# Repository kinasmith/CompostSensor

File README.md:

# Compost Sensor

> Compost Sensor is an open source sensor system for monitoring and recording the temperature and moisture of active compost. It is for small scale commercial composting operations to help with quality control and the certification processes.

This is a currently work in progress. Blog updates can be found [here](http://www.kinasmith.com/itp/spring2015/thesis/).

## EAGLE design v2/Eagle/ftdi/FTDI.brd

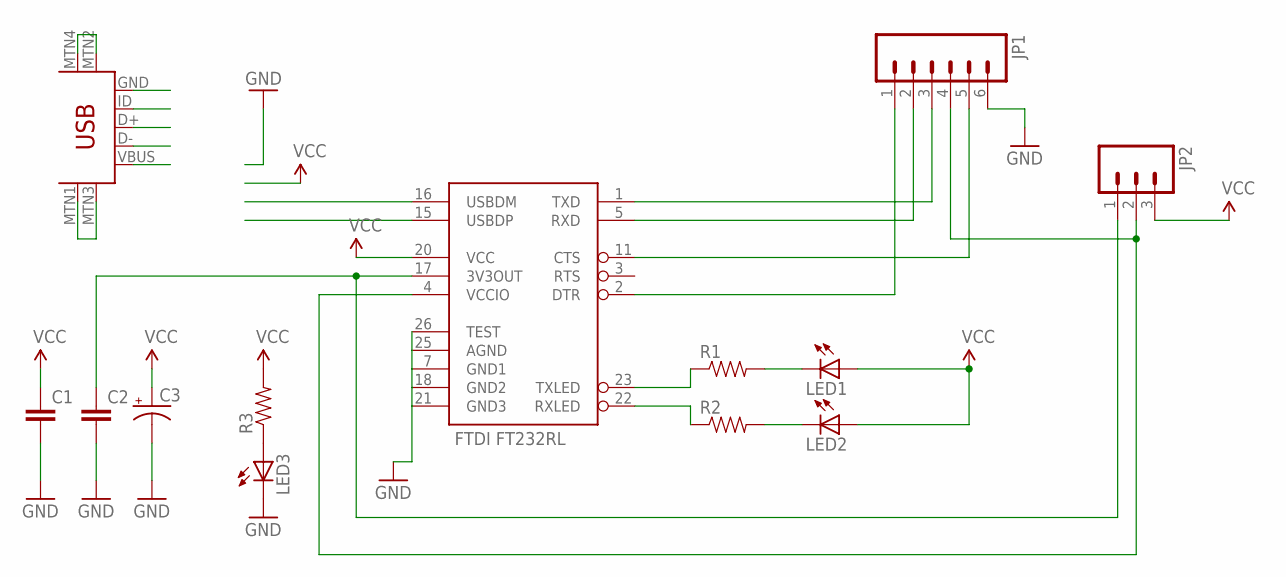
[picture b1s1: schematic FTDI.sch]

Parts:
C1, C2: CAP0603-CAP; 0603-CAP
C3: CAP_POL1206; EIA3216
JP1: M06SIP; 1X06
JP2: M03PTH; 1X03
LED1, LED2, LED3: LED0603; LED-0603
R1, R2, R3: RESISTOR0603-RES; 0603-RES
U1: FT232RL-BASICSSOP; SSOP28DB
U$3: USB-MINIB-5PIN; USB-MINIB

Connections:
D+: U1.15 (USBDP), U$3.D+
D-: U1.16 (USBDM), U$3.D-
GND: C1.2, C2.2, C3.C (-), JP1.6, LED3.C, U1.7 (GND1), U1.18 (GND2), U1.21 (GND3), U1.25 (AGND), U1.26 (TEST), U$3.GND, U$3.MTN1 (MTN2), U$3.MTN2 (MTN3), U$3.MTN3 (MTN1), U$3.MTN4
unnamed: R1.1, U1.23 (TXLED)
unnamed: LED1.C, R1.2
unnamed: LED2.C, R2.2
unnamed: R2.1, U1.22 (RXLED)
unnamed: JP1.1, U1.2 (DTR)
unnamed: JP1.2, U1.5 (RXD)
unnamed: JP1.3, U1.1 (TXD)
unnamed: JP1.5, U1.11 (CTS)
unnamed: JP1.4, JP2.2, U1.4 (VCCIO)
unnamed: C2.1, JP2.1, U1.17 (3V3OUT)
unnamed: LED3.A, R3.1
VCC: C1.1, C3.A (+), JP2.3, LED1.A, LED2.A, R3.2, U1.20 (VCC), U$3.VBUS

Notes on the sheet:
FTDI FT232RL

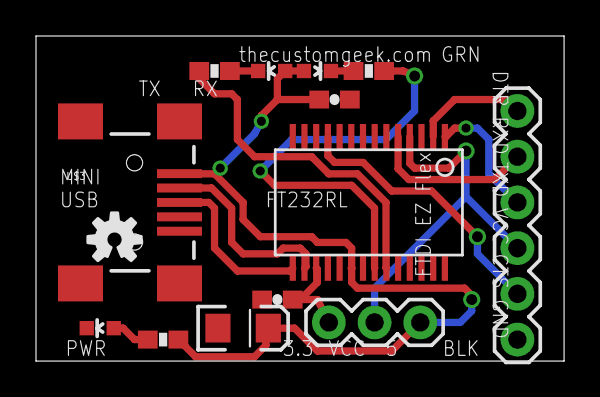
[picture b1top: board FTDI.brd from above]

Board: 2 copper layers, 29.3 x 18.1 mm, 15 parts (1 on the bottom side), 15 nets.

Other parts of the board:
U$1, U$2: OSHW-LOGO-S

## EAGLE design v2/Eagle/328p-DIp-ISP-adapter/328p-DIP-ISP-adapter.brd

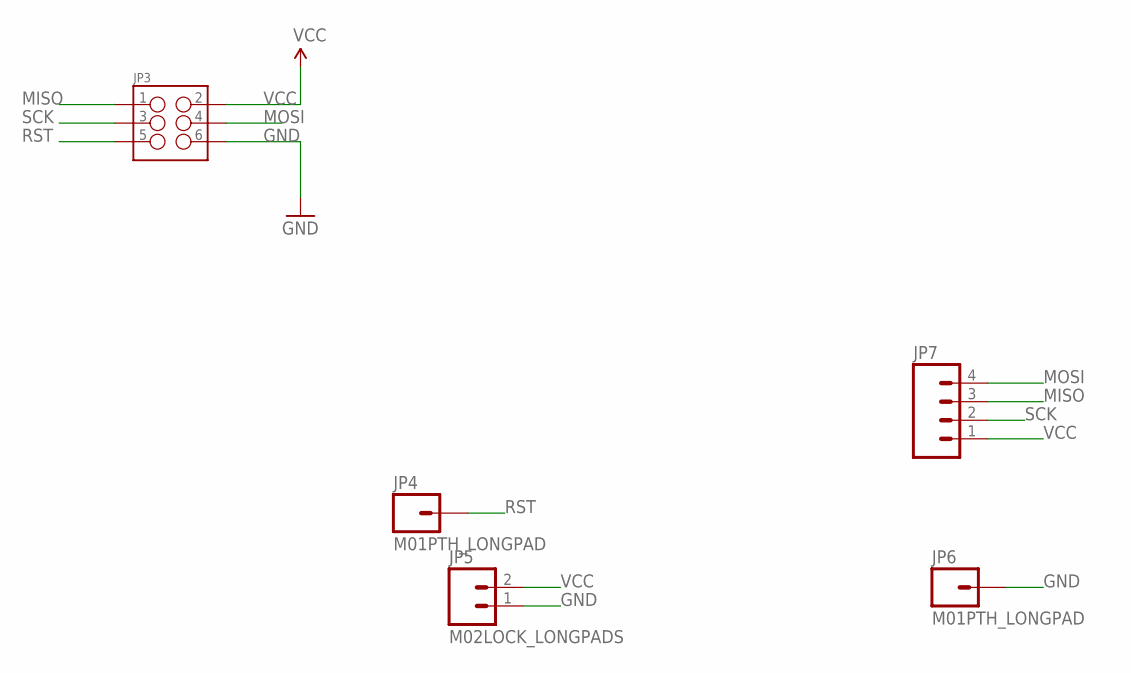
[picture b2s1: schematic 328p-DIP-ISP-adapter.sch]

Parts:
JP3: M03X2SMT; 2X3_SMT_POSTS
JP4, JP6: M01PTH_LONGPAD; 1X01_LONGPAD
JP5: M02LOCK_LONGPADS; 1X02_LOCK_LONGPADS
JP7: M04LOCK_LONGPADS; 1X04_LOCK_LONGPADS

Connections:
GND: JP3.6, JP5.1, JP6.1
MISO: JP3.1, JP7.3
MOSI: JP3.4, JP7.4
RST: JP3.5, JP4.1
SCK: JP3.3, JP7.2
VCC: JP3.2, JP5.2, JP7.1

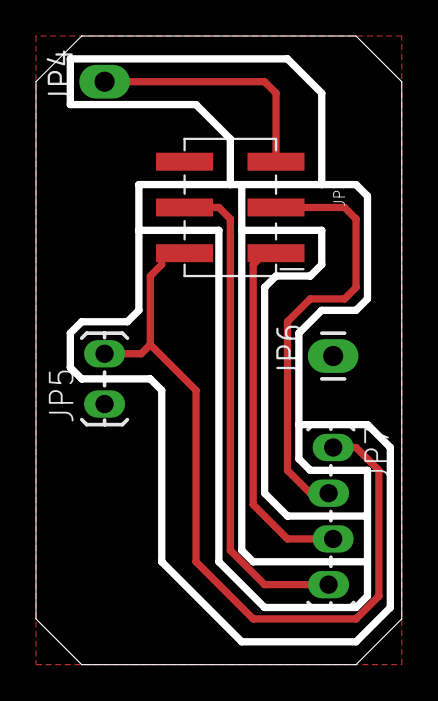
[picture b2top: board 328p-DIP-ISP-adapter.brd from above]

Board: 2 copper layers, 19.9 x 34.5 mm, 5 parts (0 on the bottom side), 6 nets.

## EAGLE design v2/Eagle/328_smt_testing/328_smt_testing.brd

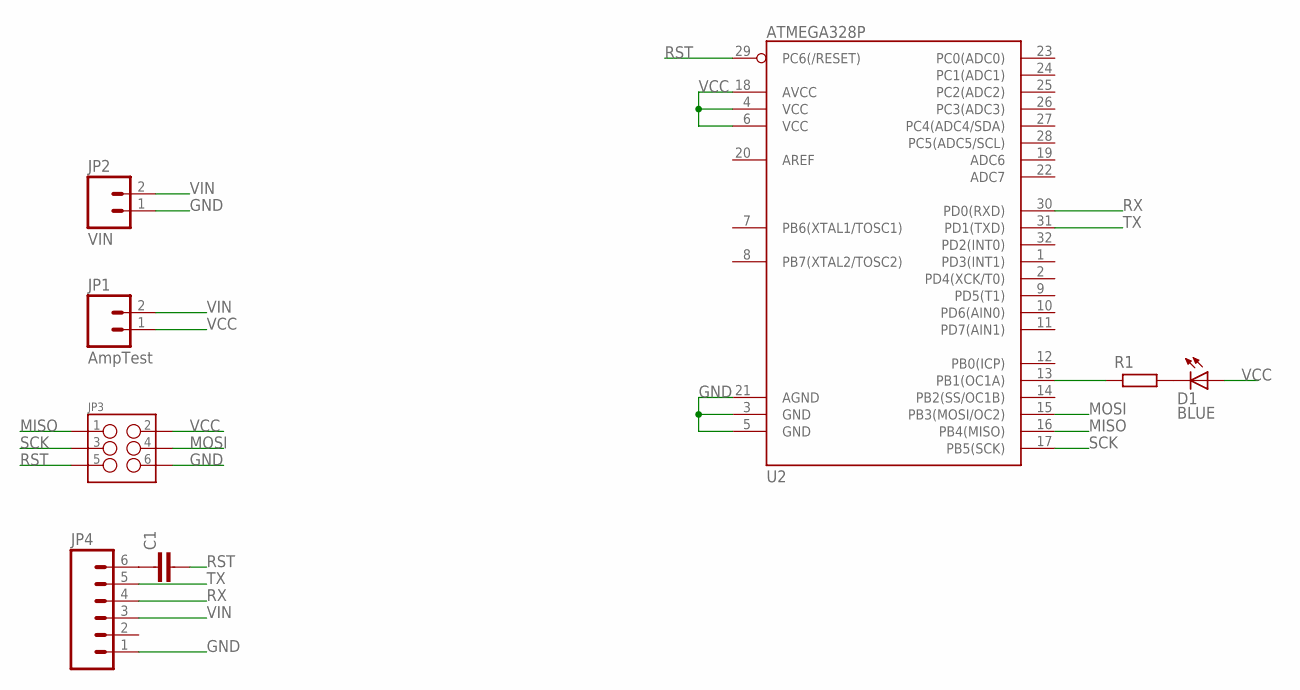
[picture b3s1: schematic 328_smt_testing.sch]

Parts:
C1: CAPACITOR0603-N; C0603-N
D1: BLUE; LED-0603
JP1: AmpTest; 1X02_LOCK_LONGPADS
JP2: VIN; 1X02_LOCK_LONGPADS
JP3: M03X2FEMALE_SMD; 2X3_SMD
JP4: M06LOCK_LONGPADS; 1X06_LOCK_LONGPADS
R1: RESISTOR0603-L; R0603-L
U2: ATMEGA328P; TQFP32-08

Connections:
GND: JP2.1, JP3.6, JP4.1, U2.3 (GND), U2.5 (GND), U2.21 (AGND)
MISO: JP3.1, U2.16 (PB4(MISO))
MOSI: JP3.4, U2.15 (PB3(MOSI/OC2))
unnamed: D1.C, R1.2
unnamed: C1.1, JP4.6
unnamed: R1.1, U2.13 (PB1(OC1A))
RST: C1.2, JP3.5, U2.29 (PC6(/RESET))
RX: JP4.4, U2.30 (PD0(RXD))
SCK: JP3.3, U2.17 (PB5(SCK))
TX: JP4.5, U2.31 (PD1(TXD))
VCC: D1.A, JP1.1, JP3.2, U2.4 (VCC), U2.6 (VCC), U2.18 (AVCC)
VIN: JP1.2, JP2.2, JP4.3

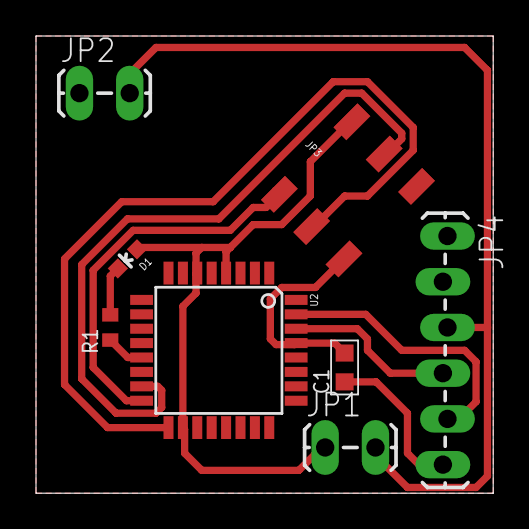
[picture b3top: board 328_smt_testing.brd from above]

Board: 2 copper layers, 25.4 x 25.4 mm, 8 parts (0 on the bottom side), 12 nets.

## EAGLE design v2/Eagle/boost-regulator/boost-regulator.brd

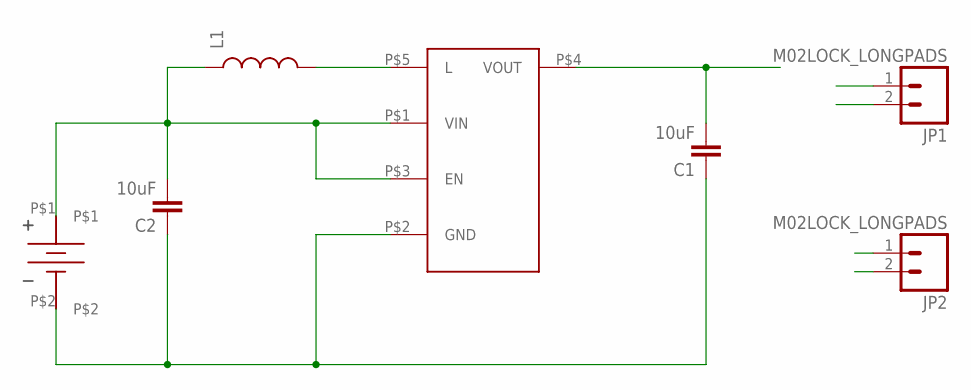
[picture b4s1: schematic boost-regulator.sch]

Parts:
C1, C2: 10uF; 0603-CAP
JP1, JP2: M02LOCK_LONGPADS; 1X02_LOCK_LONGPADS
L1: INDUCTOR0603; 0603
U$1: KEYSTONEAAHOLDER_2CELL
U$2: TPS61097-33; SOT23-5

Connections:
GND: C1.1, C2.1, JP1.2, JP2.2, U$1.P$2, U$2.P$2 (GND)
unnamed: L1.2, U$2.P$5 (L)
VCC: C1.2, JP1.1, JP2.1, U$2.P$4 (VOUT)
VIN: C2.2, L1.1, U$1.P$1, U$2.P$1 (VIN), U$2.P$3 (EN)

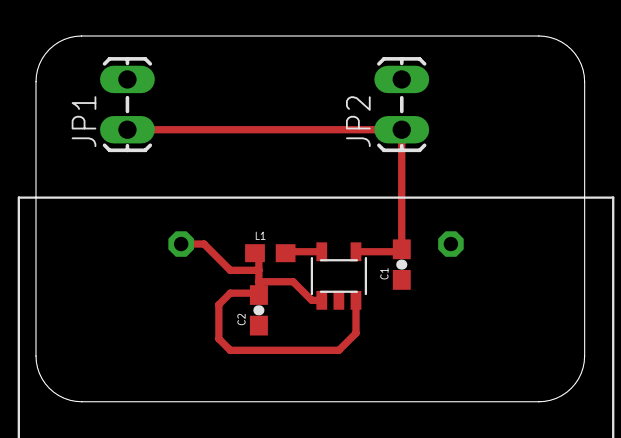
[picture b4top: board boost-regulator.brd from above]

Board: 2 copper layers, 30.5 x 20.3 mm, 7 parts (0 on the bottom side), 4 nets.

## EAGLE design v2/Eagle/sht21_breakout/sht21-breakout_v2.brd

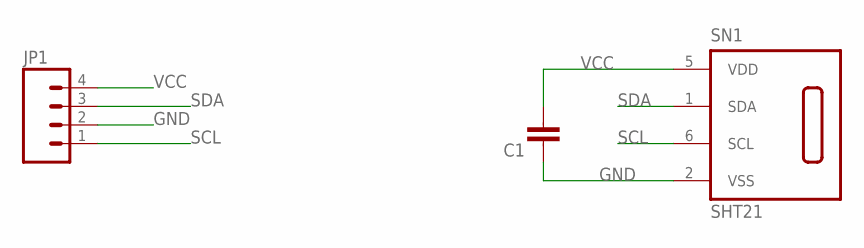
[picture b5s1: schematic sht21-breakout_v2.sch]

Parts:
C1: CAPACITOR0603-N; C0603-N
JP1: M04LONGPADS; 1X04_LONGPADS
SN1: SHT21; DFN6/SHT

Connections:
GND: C1.1, JP1.2, SN1.2 (VSS)
SCL: JP1.1, SN1.6 (SCL)
SDA: JP1.3, SN1.1 (SDA)
VCC: C1.2, JP1.4, SN1.5 (VDD)

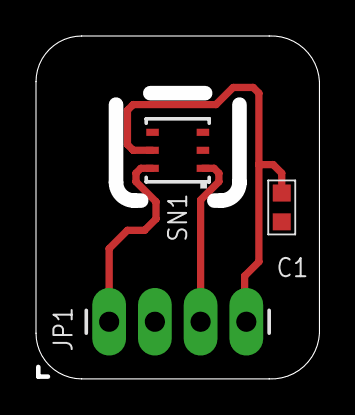
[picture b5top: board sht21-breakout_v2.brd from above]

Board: 2 copper layers, 14.9 x 18.2 mm, 3 parts (0 on the bottom side), 4 nets.

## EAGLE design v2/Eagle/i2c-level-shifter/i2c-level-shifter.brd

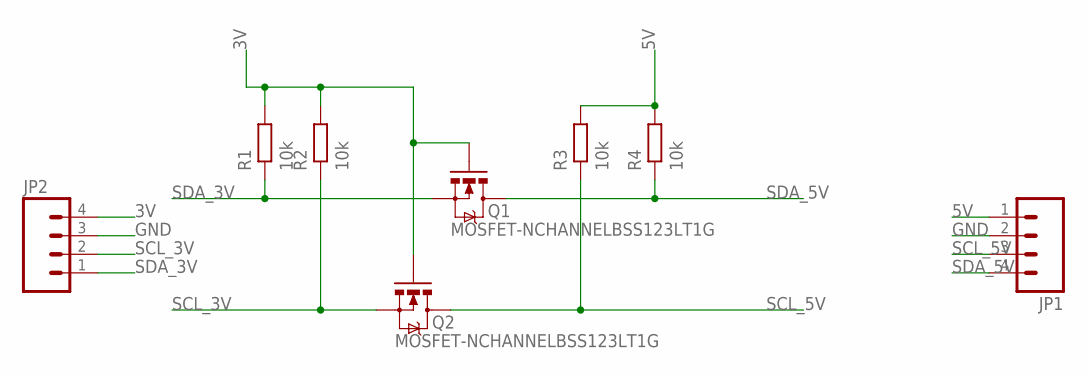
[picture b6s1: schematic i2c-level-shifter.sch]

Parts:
JP1, JP2: M04LOCK_LONGPADS; 1X04_LOCK_LONGPADS
Q1, Q2: MOSFET-NCHANNELBSS123LT1G; SOT23
R1, R2, R3, R4: 10k; R0603-N; MPN CRCW040210K0FKED

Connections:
3V: JP2.4, Q1.1 (G), Q2.1 (G), R1.2, R2.2
5V: JP1.1, R3.2, R4.2
GND: JP1.2, JP2.3
SCL_3V: JP2.2, Q2.2 (S), R2.1
SCL_5V: JP1.3, Q2.3 (D), R3.1
SDA_3V: JP2.1, Q1.2 (S), R1.1
SDA_5V: JP1.4, Q1.3 (D), R4.1

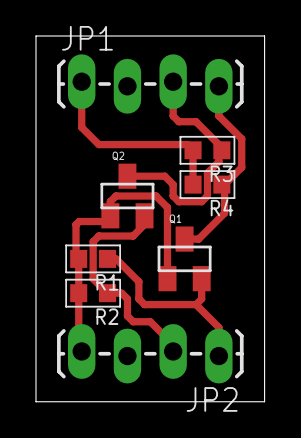
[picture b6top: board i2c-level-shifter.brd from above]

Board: 2 copper layers, 12.7 x 20.3 mm, 8 parts (0 on the bottom side), 7 nets.

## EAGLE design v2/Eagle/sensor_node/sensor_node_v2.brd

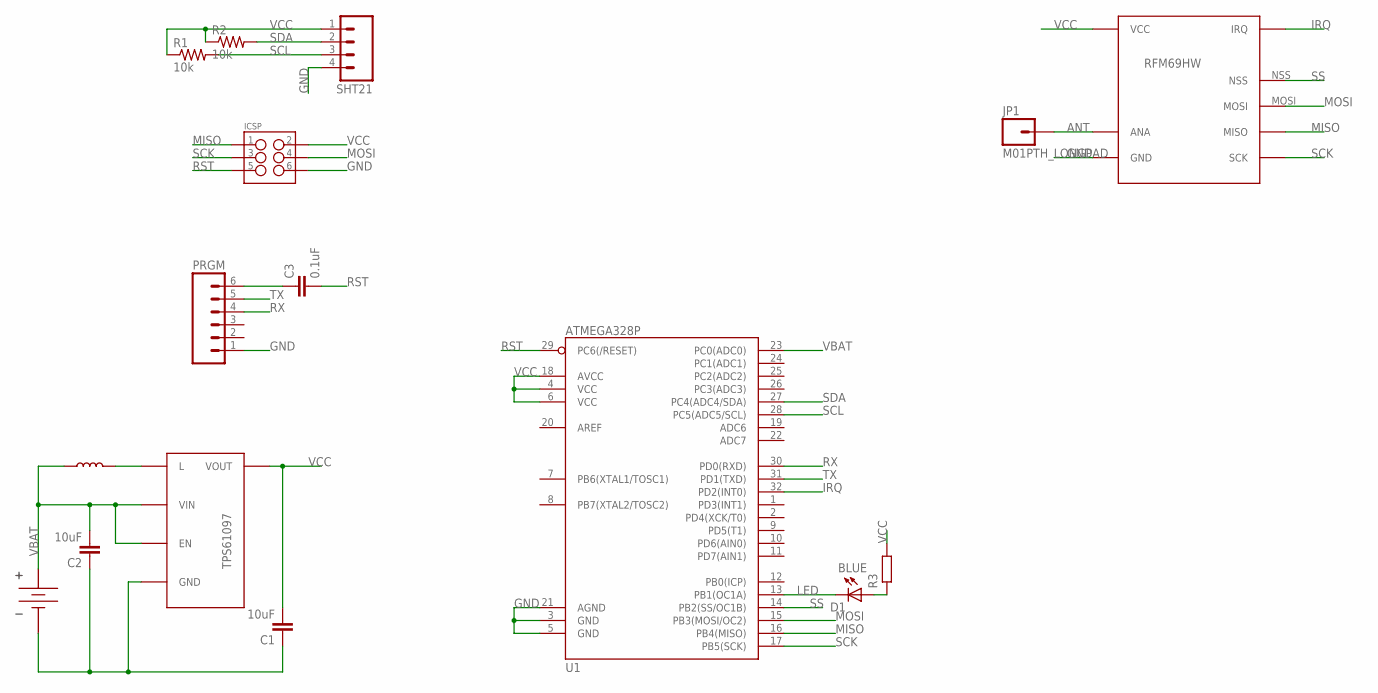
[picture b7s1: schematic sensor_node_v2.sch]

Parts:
C1, C2: 10uF; 0603-CAP
C3: 0.1uF; 0603-CAP
D1: BLUE; LED-0603
ICSP: M03X2FEMALE_SMD; 2X3_SMD
JP1: M01PTH_LONGPAD; 1X01_LONGPAD
PRGM: M06LOCK_LONGPADS; 1X06_LOCK_LONGPADS
R1, R2: 10k; 0603-RES
R3: RESISTOR0603-N; R0603-N
SHT21: M04LOCK_LONGPADS; 1X04_LOCK_LONGPADS
U1: ATMEGA328P; TQFP32-08
U$1: KEYSTONEAAHOLDER_2CELL
U$2: TPS61097-33; SOT23-5
U$3: COILCRAFT_DO3314
U$4: RFM69HW_MIN; RFM69

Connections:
ANT: JP1.1, U$4.ANA
GND: C1.1, C2.1, ICSP.6, PRGM.1, SHT21.4, U1.3 (GND), U1.5 (GND), U1.21 (AGND), U$1.P$2 (GND), U$2.P$2 (GND), U$4.GND
IRQ: U1.32 (PD2(INT0)), U$4.DIO0 (IRQ)
LED: D1.C, U1.13 (PB1(OC1A))
MISO: ICSP.1, U1.16 (PB4(MISO)), U$4.MISO
MOSI: ICSP.4, U1.15 (PB3(MOSI/OC2)), U$4.MOSI
unnamed: U$2.P$5 (L), U$3.P$1
unnamed: C3.1, PRGM.6
unnamed: D1.A, R3.1
RST: C3.2, ICSP.5, U1.29 (PC6(/RESET))
RX: PRGM.4, U1.30 (PD0(RXD))
SCK: ICSP.3, U1.17 (PB5(SCK)), U$4.SCK
SCL: R1.2, SHT21.3, U1.28 (PC5(ADC5/SCL))
SDA: R2.2, SHT21.2, U1.27 (PC4(ADC4/SDA))
SS: U1.14 (PB2(SS/OC1B)), U$4.NSS
TX: PRGM.5, U1.31 (PD1(TXD))
VBAT: C2.2, U1.23 (PC0(ADC0)), U$1.P$1 (VBAT), U$2.P$1 (VIN), U$2.P$3 (EN), U$3.P$2
VCC: C1.2, ICSP.2, R1.1, R2.1, R3.2, SHT21.1, U1.4 (VCC), U1.6 (VCC), U1.18 (AVCC), U$2.P$4 (VOUT), U$4.VCC

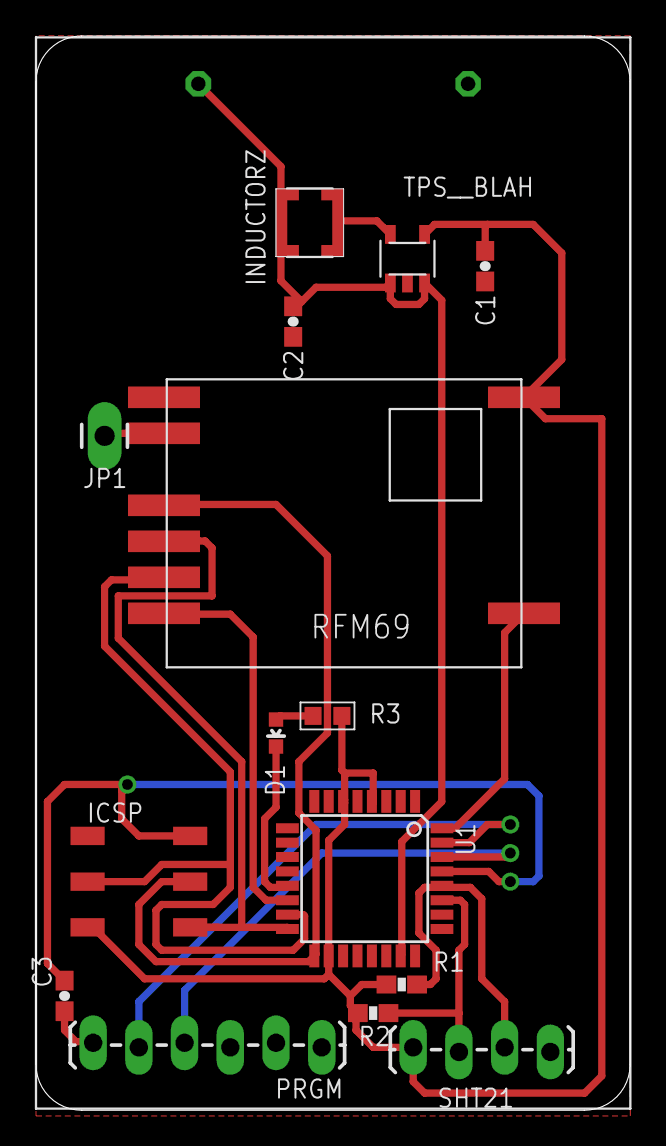
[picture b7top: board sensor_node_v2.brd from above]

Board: 2 copper layers, 33.0 x 59.7 mm, 16 parts (0 on the bottom side), 18 nets.

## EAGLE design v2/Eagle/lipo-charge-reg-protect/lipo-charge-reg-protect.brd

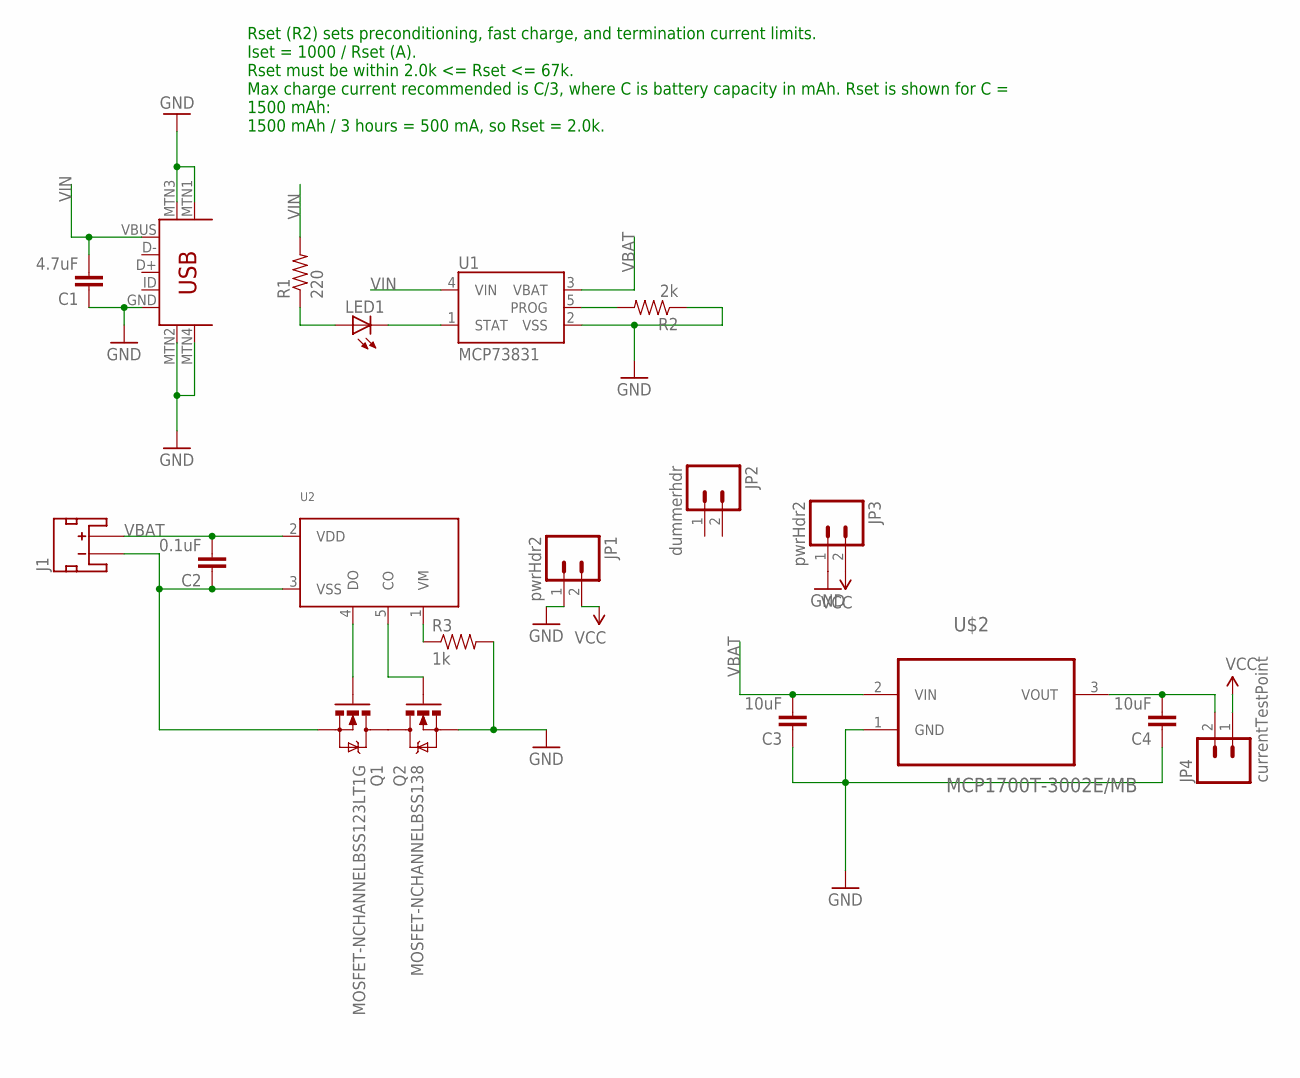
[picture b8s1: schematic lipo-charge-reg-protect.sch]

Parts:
C1: 4.7uF; 0603-CAP
C2: 0.1uF; 0603-CAP
C3, C4: 10uF; 0603-CAP
J1: JST_2MM_MALE; JST-2-SMD
JP1, JP3: pwrHdr2; 1X02_LOCK_LONGPADS
JP2: dummerhdr; 1X02_LOCK_LONGPADS
JP4: currentTestPoint; 1X02_LOCK_LONGPADS
LED1: LED0603; LED-0603
Q1: MOSFET-NCHANNELBSS123LT1G; SOT23
Q2: MOSFET-NCHANNELBSS138; SOT23
R1: 220; 0603
R2: 2k; 0603
R3: 1k; 0603
U1: MCP73831; SOT23-5
U2: S-8241; SOT23-5L
U$1: USB-MINIB-5PIN; USB-MINIB
U$2: MCP1700T-3002E/MB; SOT89

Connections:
GND: C1.1, C3.1, C4.1, JP1.1, JP3.1, Q2.2 (S), R2.1, R3.2, U1.2 (VSS), U$1.GND, U$1.MTN1 (MTN2), U$1.MTN2 (MTN3), U$1.MTN3 (MTN1), U$1.MTN4, U$2.1 (GND)
unnamed: LED1.C, U1.1 (STAT)
unnamed: LED1.A, R1.1
unnamed: R2.2, U1.5 (PROG)
unnamed: C2.1, J1.1 (-), Q1.2 (S), U2.3 (VSS)
unnamed: Q1.1 (G), U2.4 (DO)
unnamed: Q1.3 (D), Q2.3 (D)
unnamed: Q2.1 (G), U2.5 (CO)
unnamed: R3.1, U2.1 (VM)
unnamed: C4.2, JP4.2, U$2.3 (VOUT)
VBAT: C2.2, C3.2, J1.2 (+), U1.3 (VBAT), U2.2 (VDD), U$2.2 (VIN)
VCC: JP1.2, JP3.2, JP4.1
VIN: C1.2, R1.2, U1.4 (VIN), U$1.VBUS

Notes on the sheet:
Rset (R2) sets preconditioning, fast charge, and termination current limits. Iset = 1000 / Rset (A). Rset must be within 2.0k <= Rset <= 67k. Max charge current recommended is C/3, where C is battery capacity in mAh. Rset is shown for C = 1500 mAh: 1500 mAh / 3 hours = 500 mA, so Rset = 2.0k.

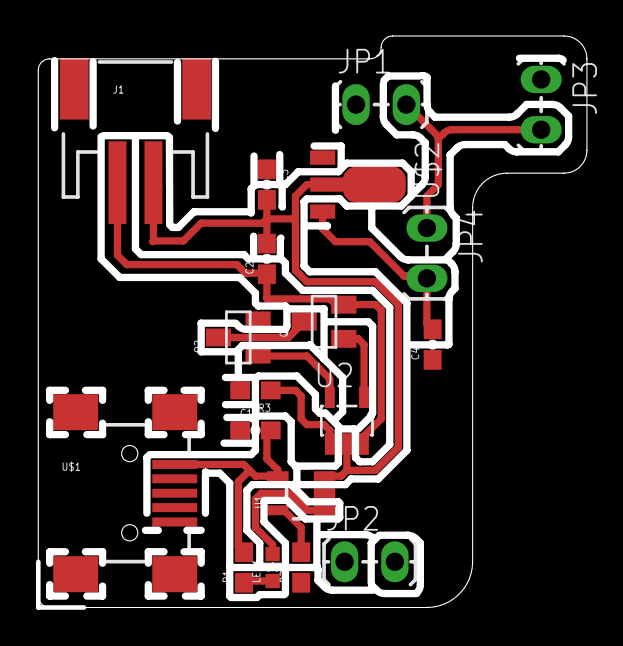
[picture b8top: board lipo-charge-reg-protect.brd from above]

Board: 2 copper layers, 30.2 x 31.5 mm, 19 parts (0 on the bottom side), 13 nets.

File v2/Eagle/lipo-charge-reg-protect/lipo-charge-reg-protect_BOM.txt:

Partlist exported from /Users/kina/Documents/eagle/thesis/lipo-charge-reg-protect.sch at 2/4/15 5:49 PM

Part Value                     Device                    Package            Description                                                                             PROD_ID     VALUE
C1   4.7uF                     0.1UF-25V(+80/-20%)(0603) 0603-CAP           CAP-00810                                                                               CAP-00810   0.1uF
C2   0.1uF                     0.1UF-25V(+80/-20%)(0603) 0603-CAP           CAP-00810                                                                               CAP-00810   0.1uF
C3   10uF                      0.1UF-25V(+80/-20%)(0603) 0603-CAP           CAP-00810                                                                               CAP-00810   0.1uF
C4   10uF                      0.1UF-25V(+80/-20%)(0603) 0603-CAP           CAP-00810                                                                               CAP-00810   0.1uF
J1                             JST_2MM_MALE              JST-2-SMD          Mates to single-cell LiPo batteries.                                                    CONN-08352       
JP1  pwrHdr2                   M02LOCK_LONGPADS          1X02_LOCK_LONGPADS Standard 2-pin 0.1" header. Use with                                                                     
JP2  dummerhdr                 M02LOCK_LONGPADS          1X02_LOCK_LONGPADS Standard 2-pin 0.1" header. Use with                                                                     
JP3  pwrHdr2                   M02LOCK_LONGPADS          1X02_LOCK_LONGPADS Standard 2-pin 0.1" header. Use with                                                                     
JP4  currentTestPoint          M02LOCK_LONGPADS          1X02_LOCK_LONGPADS Standard 2-pin 0.1" header. Use with                                                                     
LED1                           LED0603                   LED-0603           LEDs                                                                                                     
Q1   MOSFET-NCHANNELBSS123LT1G MOSFET-NCHANNELBSS123LT1G SOT23              Common NMOSFET Parts                                                                    TRANS-08345      
Q2   MOSFET-NCHANNELBSS138     MOSFET-NCHANNELBSS138     SOT23              Common NMOSFET Parts                                                                    TRANS-00830      
R1   220                       0OHM1/10W5%(0603)         0603               RES-08609                                                                               RES-08609   0    
R2   2k                        0OHM1/10W5%(0603)         0603               RES-08609                                                                               RES-08609   0    
R3   1k                        0OHM1/10W5%(0603)         0603               RES-08609                                                                               RES-08609   0    
U$1  USB-MINIB-5PIN            USB-MINIB-5PIN            USB-MINIB          Mini-USB "B" connector with 5th pin broken out.                                                          
U$2  MCP1700T-3002E/MB         MCP1700T-3002E/MB         SOT89              3.0V Low-Iq LDO - 250mA continuous current                                                               
U1   MCP73831                  MCP73831                  SOT23-5            Miniature single cell, fully integrated Li-Ion, Li-polymer charge management controller IC-09995         
U2                             S-8241                    SOT23-5L           Seiko S-8241

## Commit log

2014-06-24 added comments to tiny84 code
2014-06-24 Copied code over to non-84 fileand changed to work with normal arduino
2014-06-24 added comments to reciever Code
2014-06-24 added readme
2014-06-24 removed useless old code dir's
2014-06-24 filled out the readme better
2014-06-24 fixed a missing semicolon in the LCD startup
2014-06-25 added eagle Sch. files
2014-06-25 moved Arduino code to Arduino Folder
2014-06-25 added url to comments and changed cleaned up Readme a little
2014-06-25 added .ds_store file to repo
2014-06-25 added tiny84 senderNode schematic and board
2015-03-07 initial commit of version 2 materials
2015-03-07 added .gitignore
2015-03-07 really removed ds.store
2015-03-09 updated nodes for Absolute Humidity Math, changed the frequency of postings. Added libraries to Gateway to check size limits. Seems ok.
2015-03-11 Big Edit. Cleaned up a lot of wasted Serial Print space, added Display and Button code. Display Timeout and etc. Struggled for a long time on issues that were related to the sketch being too big for 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
2015-03-11 still having trouble with radio interferring with GSM functions. Added radio.sleep() to the start of the Post GET request. Seems to be fixed?
2015-03-24 Spring Break test
2015-03-24 test changed send interval
2015-03-25 tried implementing SLEEP in the gateway sketch, but disabling the clock will cause too many problems and isn't worth it.
2015-03-25 testing out avr_sleep in reciever
2015-03-26 added collection of libraries that are used in this project
2015-03-26 changed sleepy library in sensor node
2015-03-26 implemented the Bounce2 Library, moved the Button and screen update code to seperate functions
2015-03-26 removed empty library folders
2015-03-27 testing SD card
2015-03-27 changed the update rate for testing purposes
2015-03-27 There is not enough memory for the 328P to do all of this. I need a MEGA
2015-03-29 added junk voltage for jeelib. going to try getting voltage from FONA
2015-03-29 added simple fona comm's sketch
2015-03-29 got battery voltage to work from at AT+ command, fixed Software Serial pin assignments in Just_Talk
2015-03-31 getting gateway voltage from FONA. Also Nodes are DONE, final version upload
2015-03-31 everything is fucked....
2015-03-31 added back in Serial.print's for debug
2015-03-31 forgot a ;
2015-03-31 forgot Serial.begin
2015-03-31 checking to RX/TX
2015-03-31 everything is fucked
2015-03-31 maybe not fucked?
2015-03-31 switch to other branch
2015-04-01 everything is still fucked...fuck
2015-04-01 updated ALL of the sensor nodes
2015-04-01 Now it's not posting responses for some random reason
2015-04-01 It's FUCKING WORKING. I'mg going to switch databases now....
2015-04-01 TRYING TO MERGE JEELIB_VOLTAGE: this might break everything
2015-04-01 ADDING MORE FILES....POSSIBLE BREAKING EVERYTHING
2015-04-01 Copied in saved code to fix Fucked up Branches
2015-04-01 moved the jeelib sleepy to the node folder
2015-04-03 "changed backlightLastTime to and unsigned value. This might be the cause of the screen dying...one value rolling over and not the other?"
2015-04-05 don't know
2015-04-06 added more circuits to v2/eagle
2015-04-17 added sensorNode_v3 eagle board and updated sensor codes. Keys now live in a ._key file, which is not pushed
2015-04-19 changed the analog read pin for VBAT
2015-04-23 added comments to sensor-therm
2015-04-23 added the js files
2015-05-17 finished modifications, added moteino versions of the sensor node for thermistor and dht22
2015-05-17 added vibration sensor
2015-05-17 modified to display only relevent data from sensors
2015-05-19 changed timeout on screen
2015-05-20 modified to include SHT21 probe in demonstration

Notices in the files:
parts and their libraries:
SparkFun-LED: Licensing: CC v3.0 Share-Alike You are welcome to use this library for commercial purposes.
sensirion: Copyright (C) 2011, Bob Starr
